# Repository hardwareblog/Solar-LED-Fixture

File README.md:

# Solar-LED-Fixture
Outdoor solar LED light schematics and board layout files.

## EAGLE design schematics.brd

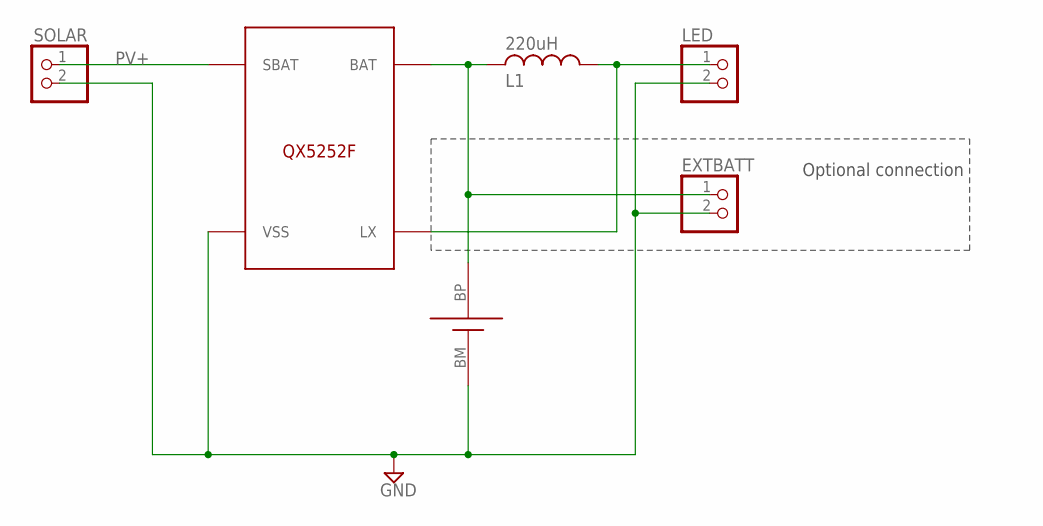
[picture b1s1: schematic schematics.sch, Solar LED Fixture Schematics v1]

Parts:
EXTBATT: PINHD-1X2; 1X02
L1: 220uH; 0204/7
LED: PINHD-1X2; 1X02
SOLAR: PINHD-1X2; 1X02
U$1: QX5252F; TO-94
U$2: NIMHCOINBAT; 12VNIMHBAT

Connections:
B+: EXTBATT.1, L1.2, U$1.BAT, U$2.BP (VCC)
GND: EXTBATT.2, LED.2, SOLAR.2, U$1.VSS, U$2.BM (GND)
LX: L1.1, LED.1, U$1.LX
PV+: SOLAR.1, U$1.SBAT

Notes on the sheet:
Optional connection

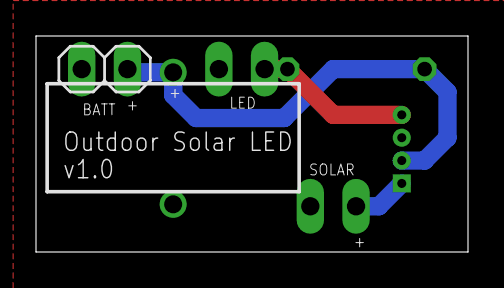
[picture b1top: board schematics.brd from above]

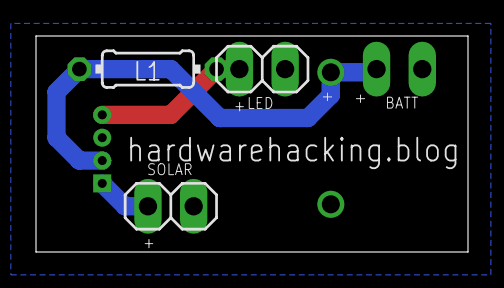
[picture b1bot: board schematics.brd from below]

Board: 2 copper layers, 24.0 x 12.0 mm, 6 parts (3 on the bottom side), 4 nets.

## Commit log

2019-11-24 First Release

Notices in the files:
parts and their libraries:
SparkFun-Aesthetics: Licensing: Creative Commons ShareAlike 4.0 International - https://creativecommons.org/licenses/by-sa/4.0
